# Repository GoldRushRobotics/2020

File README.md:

# CAR's Repo for 2020 Competition - Pi Day!

Team Lead: Matt Wells

To find out more about the compeition, visit the [official Github](https://github.com/ncgadgetry/southeastcon2020) for this year's competition!

## How to use GitHub

#### Install Git
First thing's first, make sure you have git installed on your computer. If you don't have it installed, you can install it from [here](https://git-scm.com/downloads).

#### Clone the Repo
Next let's clone this repo. Open your command line, terminal, or bash and navigate to the directory in which you want to put all of the code.

Once you're in the directory you want the code to be in, simply type in:
```
git clone https://github.com/car-robotics/2020.git
```
You should now see a new folder in your current directory called `2020`.

Boom! You now have the most up to date code from the repo. You don't have to clone the repo everytime you want to get updates, however. 

#### Git Pull - Get most up to date code
To get the most up to date code, type in:
```
git pull
```
This will pull in the most up to date changes from the repo. It is a good idea to pull updates before you start coding and before you push your code up to the repo to make sure you are editing and pushing the most up to date stuff.

#### Staging Changes to be Committed
If you're ready to push your code, and you've already pulled to make sure you have the most up to date, you will first need to stage your changes. Simply running:
```
git add .
```
will stage all of your changes to be committed. This will show you all of the things that you have changed. 

#### Committing Changes
If everything looks right, it's time to commit. Run the command:
```
git commit -m "Your message here"
```
Add your message that briefly describes the changes you've made.

#### Pushing Changes
Now that you have committed, and there are no merge conflicts, you can push those committed changes up to the repo.
```
git push
```
Will push all committed changes.

#### Merge Conflicts
If you ever have merge conflicts, ask Matt for help unless you know for certain what you are doing.

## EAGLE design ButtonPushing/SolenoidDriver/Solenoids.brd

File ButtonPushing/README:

Button Pushing section of the repo

Members:
  Will
  Sam
  Evan
  Samuel
  Moises
  Afif
  Lucas

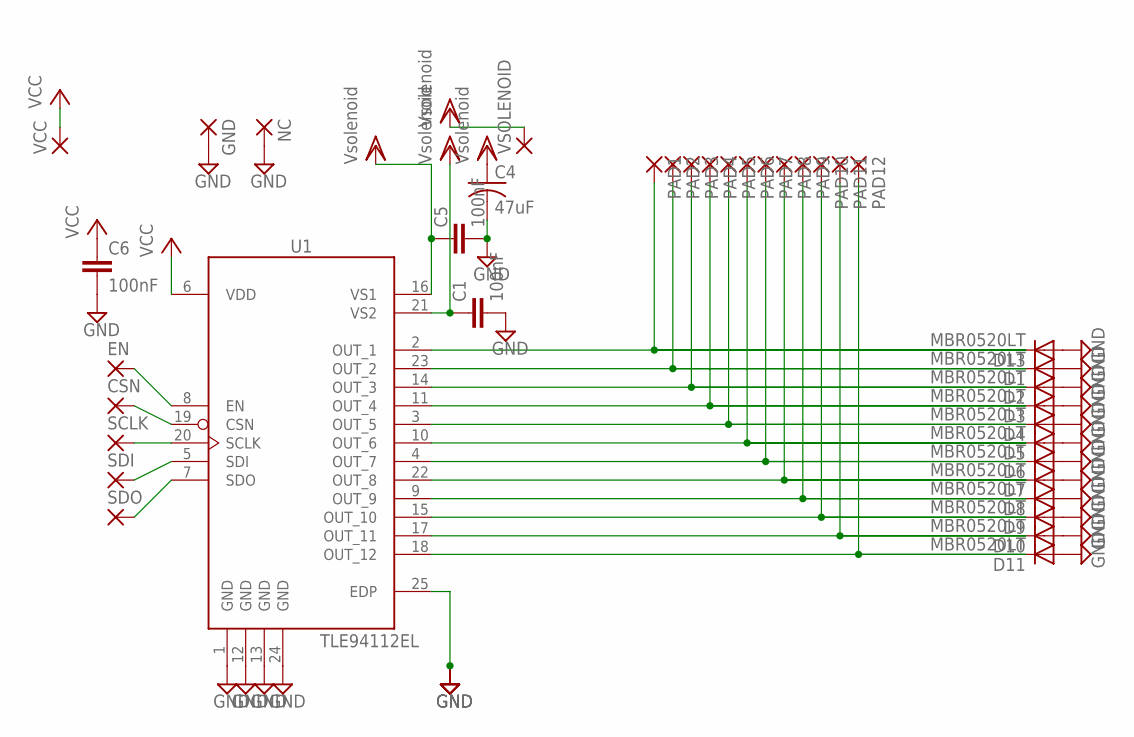
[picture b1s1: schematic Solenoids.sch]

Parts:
C1, C5, C6: 100nF; C0402K
C4: 47uF; C050-045X075
CSN: 1,6/0,8
D1, D2, D3, D4, D5, D6, D7, D8, D9, D10, D11, D13: MBR0520LT; SOD123
EN: 1,6/0,8
GND: 1,6/0,8
NC: 1,6/0,8
PAD1, PAD2, PAD3, PAD4, PAD5, PAD6, PAD7, PAD8, PAD9, PAD10, PAD11, PAD12: 1,6/0,8
SCLK: 1,6/0,8
SDI: 1,6/0,8
SDO: 1,6/0,8
U1: TLE94112EL; SOP65P600X170-25N
VCC: 1,6/0,8
VSOLENOID: 1,6/0,8

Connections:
GND: C1.2, C4.2, C5.2, C6.2, D1.A, D2.A, D3.A, D4.A, D5.A, D6.A, D7.A, D8.A, D9.A, D10.A, D11.A, D13.A, GND.1, NC.1, U1.1 (GND), U1.12 (GND), U1.13 (GND), U1.24 (GND), U1.25 (EDP); also elsewhere on the board
unnamed: D13.C, PAD1.1, U1.2 (OUT_1)
unnamed: D1.C, PAD2.1, U1.23 (OUT_2)
unnamed: D2.C, PAD3.1, U1.14 (OUT_3)
unnamed: D3.C, PAD4.1, U1.11 (OUT_4)
unnamed: D4.C, PAD5.1, U1.3 (OUT_5)
unnamed: D5.C, PAD6.1, U1.10 (OUT_6)
unnamed: D6.C, PAD7.1, U1.4 (OUT_7)
unnamed: D7.C, PAD8.1, U1.22 (OUT_8)
unnamed: D8.C, PAD9.1, U1.9 (OUT_9)
unnamed: D9.C, PAD10.1, U1.15 (OUT_10)
unnamed: D10.C, PAD11.1, U1.17 (OUT_11)
unnamed: D11.C, PAD12.1, U1.18 (OUT_12)
unnamed: EN.1, U1.8 (EN)
unnamed: CSN.1, U1.19 (CSN)
unnamed: SCLK.1, U1.20 (SCLK)
unnamed: SDI.1, U1.5 (SDI)
unnamed: SDO.1, U1.7 (SDO)
VCC: C6.1, U1.6 (VDD), VCC.1
VDD: C1.1, C4.1, C5.1, U1.16 (VS1), U1.21 (VS2), VSOLENOID.1; also elsewhere on the board

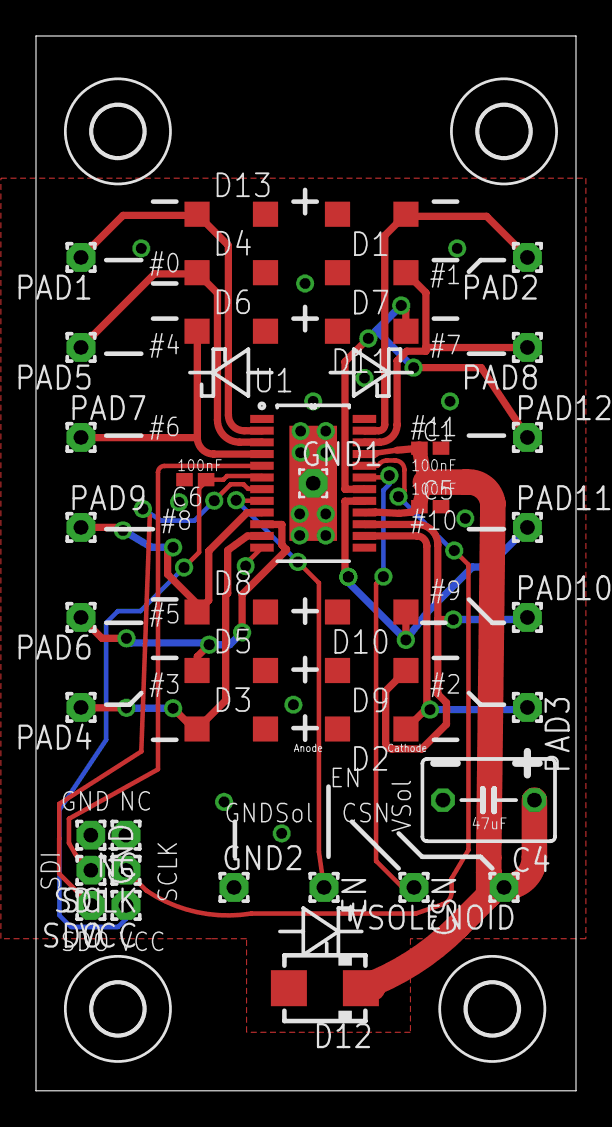
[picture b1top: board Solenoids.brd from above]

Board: 2 copper layers, 30.0 x 58.6 mm, 45 parts (0 on the bottom side), 20 nets.

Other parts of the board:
D12: MBRA340T3; SMA
GND1, GND2: 1,6/0,8
H1, H2, H3, H4: MOUNT-HOLE2.8; 2,8

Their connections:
GND: D12.A, GND1.1, GND2.1; also elsewhere on the board
VDD: D12.C; also elsewhere on the board

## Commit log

2019-08-23 Add member names
2019-09-02 Added code for button simulator
2019-09-06 Add files via upload
    Solenoid program
2019-09-09 Fixing Samofuture's file structure mistake.
2019-09-09 Add Github Instructions
2019-09-09 Added official arena control system
2019-09-14 Test commit
2019-09-14 Leedle
2019-09-14 Code for Theodore
2019-09-17 Yaw is now in double form
2019-09-17 Stacking CAD 1.0
2019-09-19 Code for Gyro Added
2019-09-20 Shift register support, more Pi
2019-09-26 Added Motor Shield/H-bridge solenoid control code
2019-09-27 Shield code works and fits in UNO's memory limit
2019-09-30 Working Gyro Data
2019-10-04 Gyro Heading Updated
2019-10-04 Gyro Heading Updated2
2019-10-10 RAPID FIRE!!!
    Or in more boring terms, I used low level functions within the library to get the solenoids to fire in 30ms intervals
2019-10-10 Got the cycle time down to 25ms
2019-10-11 driving infrastructure, new imu
2019-10-11 cleaned up Drive code (split into 3 .ino files)
2019-10-11 Deleting unnecessary file
2019-10-11 Removing unnecessary file
2019-10-11 Organizing folder
2019-10-12 Schematic almost complete, some routing progress
    Having thru-hole (or at least, individually packaged) diodes may give us more design flexibility, but I am still investigating which components to use (specifically where to put screw terminals and h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
2019-10-12 Rename ButtonPushing/SolenoidDriver/BAT160A.lbr to ButtonPushing/SolenoidDriverPCB/BAT160A.lbr
2019-10-12 Ugh, wrong initial folder name
2019-10-12 I will need to fix the folder name later so it includes "PCB" so everybody knows what's in this folder
2019-10-14 Removed redundant code and added limit switch
2019-10-14 Added second limit switch and comments
2019-10-17 cleaned up code some more, pulled light sensor code into class
2019-10-21 added code for encoders
2019-10-24 Writing comments for code -Very confused
2019-10-24 More comments
2019-10-24 Distance from encoder method added
2019-10-24 Encoder distance tick corrected
2019-10-24 distance from encoder formula perfected
2019-10-24 More distance /encoder stuff
2019-10-25 Correction to distance encoder stuff
2019-11-16 encoder stuff
2020-01-14 Light sensor working
2020-01-18 Fully routed PCB
    Basically done, but needs to be checked over
2020-01-21 Working code with pullup resistors and correct detection
2020-01-30 Add files via upload
    This code tests the light sensors. That is it.
2020-01-31 Add files via upload
    Updated code. Line follows, checks the bar count, turn using imu, goes straight into the pocket using imu
2020-02-01 Add files via upload
    update, we changed some constant values. The line following works and the gyro driving works well. This code drives to the 5th bar and turns 90degrees and drives into pocket
2020-02-04 Add files via upload
    This code works completely, follows line for bar count 5, turns 90, goes into pocket, leaves the pocket, turns 90, follows line for bar count 1 and ends with a turn to heading to make sure we are str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
2020-02-04 Fix Dylan's mistake >:(
2020-02-05 Adjusted degree threshold
2020-02-06 Here it is the code from online(runs stepper)
2020-02-06 servo code that went missing
2020-02-08 Added grabber servo to main code
2020-02-13 Added code for (finger?) mechanism to deploy button pusher
2020-02-13 Built version revision 1
2020-02-14 Stepper has been implemented with raiseStack and lowerStack
2020-02-14 Fixed stepper count value
2020-02-25 Current Solenoid code as of 2/25/20
2020-02-26 Code for testing pins
2020-02-28 Repeated push delay added
2020-02-29 Code tweaks for new electrical
2020-03-05 working drivinggit add .!
2020-03-05 Added lifting to main code
2020-03-12 Kicker code
2020-03-14 Added delivery code
2020-03-14 Final Update YAYgit add .git add .
